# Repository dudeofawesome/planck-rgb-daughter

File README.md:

# planck-rgb-daughter

Daughter-board to add RGB switch lighting to the [OLKB Planck Keyboard](https://olkb.com/planck)

## Libraries used
- adafruit
- capacitor-wima
- resistor
- SparkFun Aesthetics
- SparkFun-Connectors
- SparkFun-PowerSymbols

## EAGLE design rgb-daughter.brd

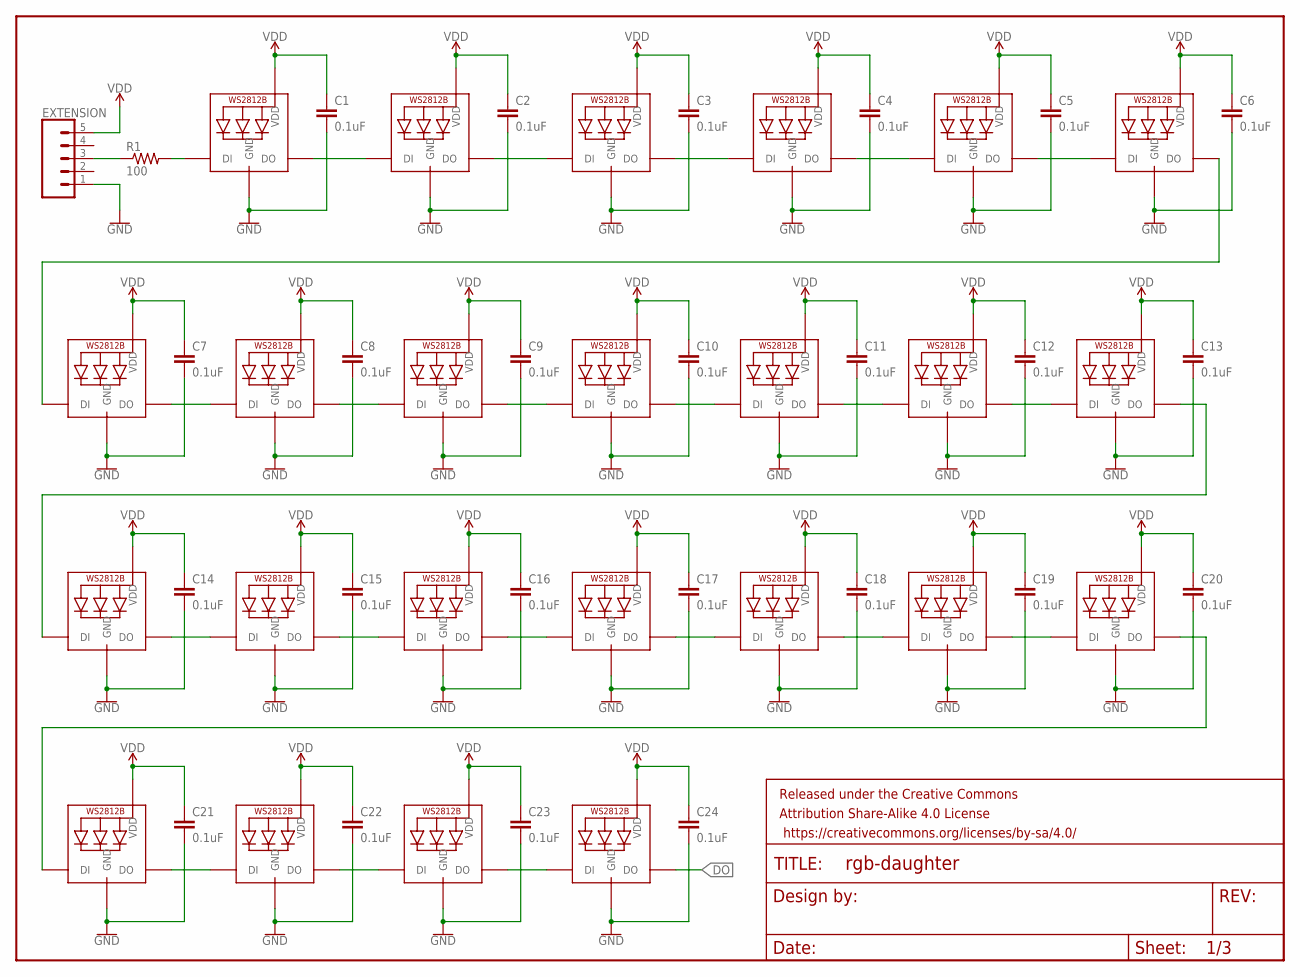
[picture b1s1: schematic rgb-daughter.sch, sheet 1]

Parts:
C1, C2, C3, C4, C5, C6, C7, C8, C9, C10, C11, C12, C13, C14, C15, C16, C17, C18, C19, C20, C21, C22, C23, C24: 0.1uF; 0603
EXTENSION: CONN_051.27MM; 1X05_1.27MM
FRAME1: FRAME-LETTER; CREATIVE_COMMONS
LED1, LED2, LED3, LED4, LED5, LED6, LED7, LED8, LED9, LED10, LED11, LED12, LED13, LED14, LED15, LED16, LED17, LED18, LED19, LED20, LED21, LED22, LED23, LED24: WS2812B3535; LED3535
R1: 100; M0805

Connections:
DO: LED24.3 (DO); also elsewhere on the board
GND: C1.2, C2.2, C3.2, C4.2, C5.2, C6.2, C7.2, C8.2, C9.2, C10.2, C11.2, C12.2, C13.2, C14.2, C15.2, C16.2, C17.2, C18.2, C19.2, C20.2, C21.2, C22.2, C23.2, C24.2, EXTENSION.1, LED1.4 (GND), LED2.4 (GND), LED3.4 (GND), LED4.4 (GND), LED5.4 (GND), LED6.4 (GND), LED7.4 (GND), LED8.4 (GND), LED9.4 (GND), LED10.4 (GND), LED11.4 (GND), LED12.4 (GND), LED13.4 (GND), LED14.4 (GND), LED15.4 (GND), LED16.4 (GND), LED17.4 (GND), LED18.4 (GND), LED19.4 (GND), LED20.4 (GND), LED21.4 (GND), LED22.4 (GND), LED23.4 (GND), LED24.4 (GND); also elsewhere on the board
unnamed: LED1.1 (DI), R1.2
unnamed: LED1.3 (DO), LED2.1 (DI)
unnamed: EXTENSION.3, R1.1
unnamed: LED2.3 (DO), LED3.1 (DI)
unnamed: LED3.3 (DO), LED4.1 (DI)
unnamed: LED4.3 (DO), LED5.1 (DI)
unnamed: LED5.3 (DO), LED6.1 (DI)
unnamed: LED7.3 (DO), LED8.1 (DI)
unnamed: LED8.3 (DO), LED9.1 (DI)
unnamed: LED9.3 (DO), LED10.1 (DI)
unnamed: LED10.3 (DO), LED11.1 (DI)
unnamed: LED11.3 (DO), LED12.1 (DI)
unnamed: LED12.3 (DO), LED13.1 (DI)
unnamed: LED13.3 (DO), LED14.1 (DI)
unnamed: LED14.3 (DO), LED15.1 (DI)
unnamed: LED15.3 (DO), LED16.1 (DI)
unnamed: LED16.3 (DO), LED17.1 (DI)
unnamed: LED17.3 (DO), LED18.1 (DI)
unnamed: LED18.3 (DO), LED19.1 (DI)
unnamed: LED19.3 (DO), LED20.1 (DI)
unnamed: LED20.3 (DO), LED21.1 (DI)
unnamed: LED21.3 (DO), LED22.1 (DI)
unnamed: LED22.3 (DO), LED23.1 (DI)
unnamed: LED23.3 (DO), LED24.1 (DI)
unnamed: LED6.3 (DO), LED7.1 (DI)
VDD: C1.1, C2.1, C3.1, C4.1, C5.1, C6.1, C7.1, C8.1, C9.1, C10.1, C11.1, C12.1, C13.1, C14.1, C15.1, C16.1, C17.1, C18.1, C19.1, C20.1, C21.1, C22.1, C23.1, C24.1, EXTENSION.5, LED1.2 (VDD), LED2.2 (VDD), LED3.2 (VDD), LED4.2 (VDD), LED5.2 (VDD), LED6.2 (VDD), LED7.2 (VDD), LED8.2 (VDD), LED9.2 (VDD), LED10.2 (VDD), LED11.2 (VDD), LED12.2 (VDD), LED13.2 (VDD), LED14.2 (VDD), LED15.2 (VDD), LED16.2 (VDD), LED17.2 (VDD), LED18.2 (VDD), LED19.2 (VDD), LED20.2 (VDD), LED21.2 (VDD), LED22.2 (VDD), LED23.2 (VDD), LED24.2 (VDD); also elsewhere on the board

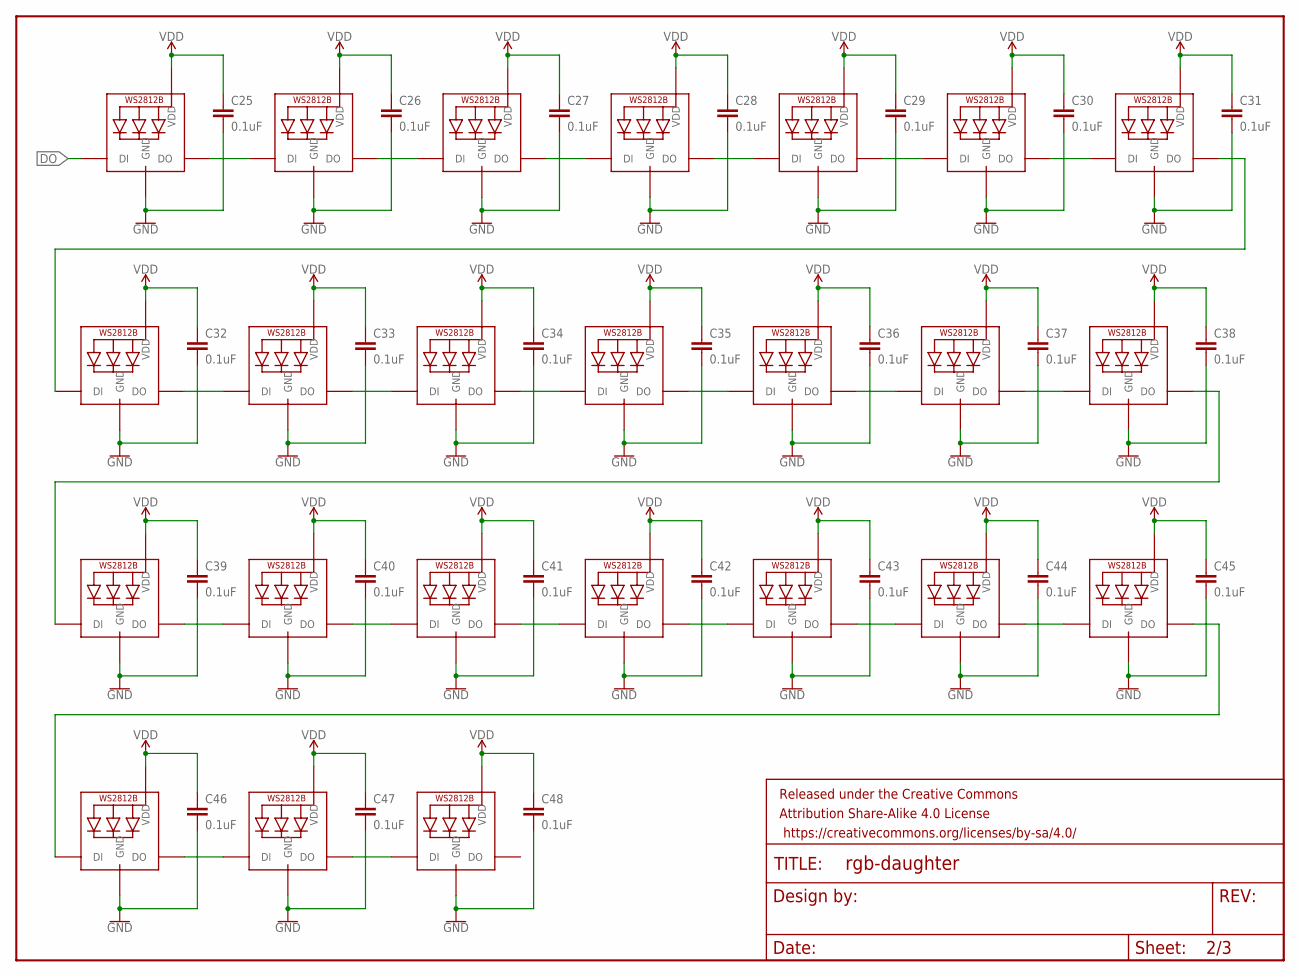
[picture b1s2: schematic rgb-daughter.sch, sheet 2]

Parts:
C25, C26, C27, C28, C29, C30, C31, C32, C33, C34, C35, C36, C37, C38, C39, C40, C41, C42, C43, C44, C45, C46, C47, C48: 0.1uF; 0603
FRAME2: FRAME-LETTER; CREATIVE_COMMONS
LED25, LED26, LED27, LED28, LED29, LED30, LED31, LED32, LED33, LED34, LED35, LED36, LED37, LED38, LED39, LED40, LED41, LED42, LED43, LED44, LED45, LED46, LED47, LED48: WS2812B3535; LED3535

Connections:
DO: LED25.1 (DI); also elsewhere on the board
GND: C25.2, C26.2, C27.2, C28.2, C29.2, C30.2, C31.2, C32.2, C33.2, C34.2, C35.2, C36.2, C37.2, C38.2, C39.2, C40.2, C41.2, C42.2, C43.2, C44.2, C45.2, C46.2, C47.2, C48.2, LED25.4 (GND), LED26.4 (GND), LED27.4 (GND), LED28.4 (GND), LED29.4 (GND), LED30.4 (GND), LED31.4 (GND), LED32.4 (GND), LED33.4 (GND), LED34.4 (GND), LED35.4 (GND), LED36.4 (GND), LED37.4 (GND), LED38.4 (GND), LED39.4 (GND), LED40.4 (GND), LED41.4 (GND), LED42.4 (GND), LED43.4 (GND), LED44.4 (GND), LED45.4 (GND), LED46.4 (GND), LED47.4 (GND), LED48.4 (GND); also elsewhere on the board
unnamed: LED25.3 (DO), LED26.1 (DI)
unnamed: LED26.3 (DO), LED27.1 (DI)
unnamed: LED27.3 (DO), LED28.1 (DI)
unnamed: LED28.3 (DO), LED29.1 (DI)
unnamed: LED29.3 (DO), LED30.1 (DI)
unnamed: LED30.3 (DO), LED31.1 (DI)
unnamed: LED31.3 (DO), LED32.1 (DI)
unnamed: LED32.3 (DO), LED33.1 (DI)
unnamed: LED33.3 (DO), LED34.1 (DI)
unnamed: LED34.3 (DO), LED35.1 (DI)
unnamed: LED35.3 (DO), LED36.1 (DI)
unnamed: LED36.3 (DO), LED37.1 (DI)
unnamed: LED37.3 (DO), LED38.1 (DI)
unnamed: LED38.3 (DO), LED39.1 (DI)
unnamed: LED39.3 (DO), LED40.1 (DI)
unnamed: LED40.3 (DO), LED41.1 (DI)
unnamed: LED41.3 (DO), LED42.1 (DI)
unnamed: LED42.3 (DO), LED43.1 (DI)
unnamed: LED43.3 (DO), LED44.1 (DI)
unnamed: LED44.3 (DO), LED45.1 (DI)
unnamed: LED45.3 (DO), LED46.1 (DI)
unnamed: LED46.3 (DO), LED47.1 (DI)
unnamed: LED47.3 (DO), LED48.1 (DI)
VDD: C25.1, C26.1, C27.1, C28.1, C29.1, C30.1, C31.1, C32.1, C33.1, C34.1, C35.1, C36.1, C37.1, C38.1, C39.1, C40.1, C41.1, C42.1, C43.1, C44.1, C45.1, C46.1, C47.1, C48.1, LED25.2 (VDD), LED26.2 (VDD), LED27.2 (VDD), LED28.2 (VDD), LED29.2 (VDD), LED30.2 (VDD), LED31.2 (VDD), LED32.2 (VDD), LED33.2 (VDD), LED34.2 (VDD), LED35.2 (VDD), LED36.2 (VDD), LED37.2 (VDD), LED38.2 (VDD), LED39.2 (VDD), LED40.2 (VDD), LED41.2 (VDD), LED42.2 (VDD), LED43.2 (VDD), LED44.2 (VDD), LED45.2 (VDD), LED46.2 (VDD), LED47.2 (VDD), LED48.2 (VDD); also elsewhere on the board

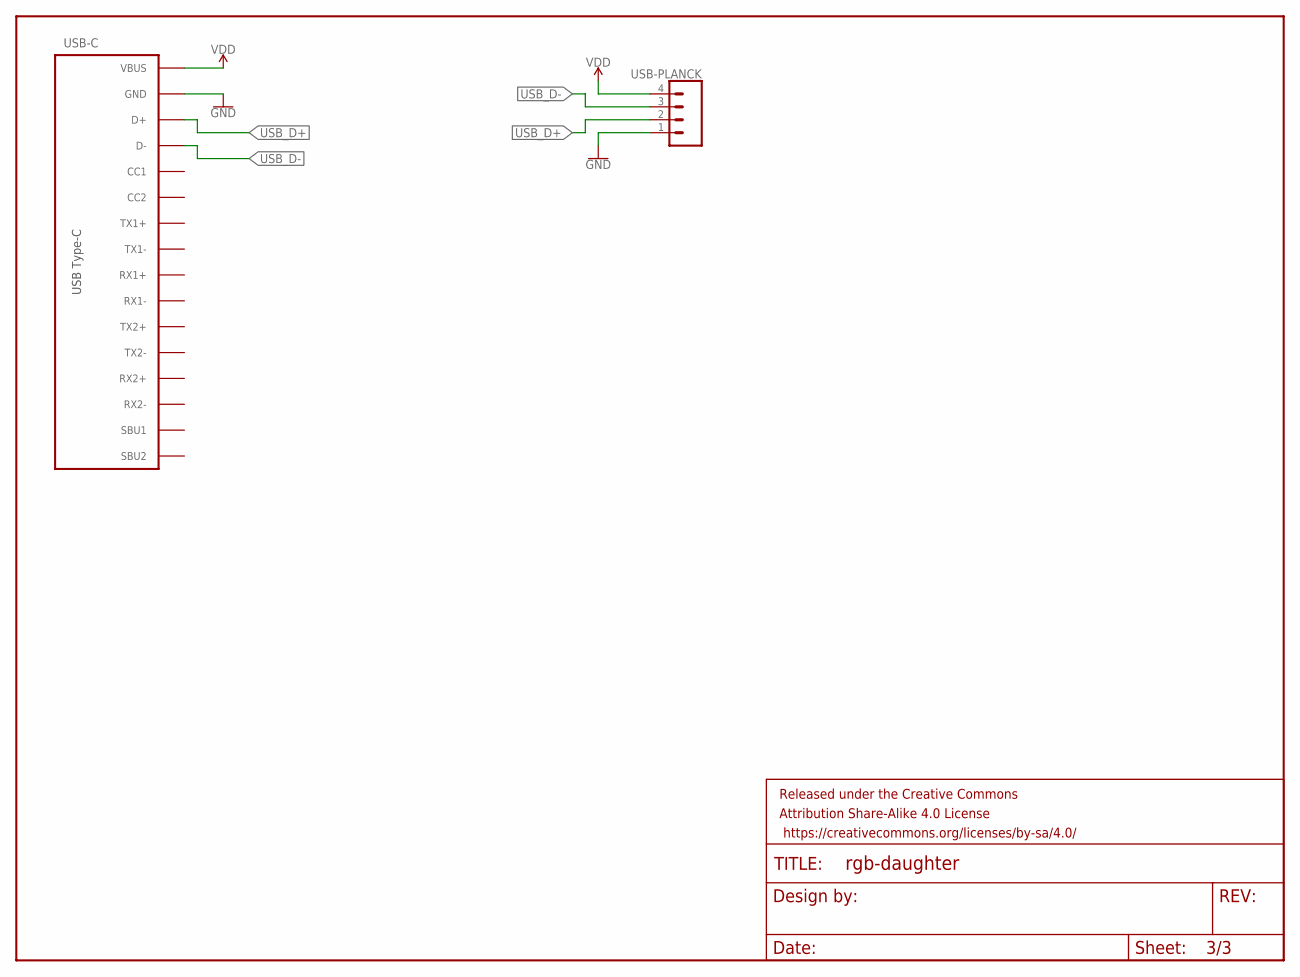
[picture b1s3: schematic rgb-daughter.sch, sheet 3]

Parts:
FRAME3: FRAME-LETTER; CREATIVE_COMMONS
USB-C: USB-TYPE-CDX07S024JJ3R1300; DX07S024JJ3R1300
USB-PLANCK: CONN_041.27MM; 1X04_1.27MM

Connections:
GND: USB-C.A1 (GND), USB-C.A12 (GND), USB-C.B1 (GND), USB-C.B12 (GND), USB-C.GND@1 (GND), USB-C.GND@2 (GND), USB-C.GND@3 (GND), USB-C.GND@4 (GND), USB-C.GND@5 (GND), USB-C.GND@6 (GND), USB-PLANCK.1; also elsewhere on the board
RX1+: USB-C.B11 (RX1+)
SBU2: USB-C.B8 (SBU2)
TX2-: USB-C.B3 (TX2-)
USB_D+: USB-C.A6 (D+), USB-C.B6 (D+), USB-PLANCK.2
USB_D-: USB-C.A7 (D-), USB-C.B7 (D-), USB-PLANCK.3
VDD: USB-C.A4 (VBUS), USB-C.A9 (VBUS), USB-C.B4 (VBUS), USB-C.B9 (VBUS), USB-PLANCK.4; also elsewhere on the board

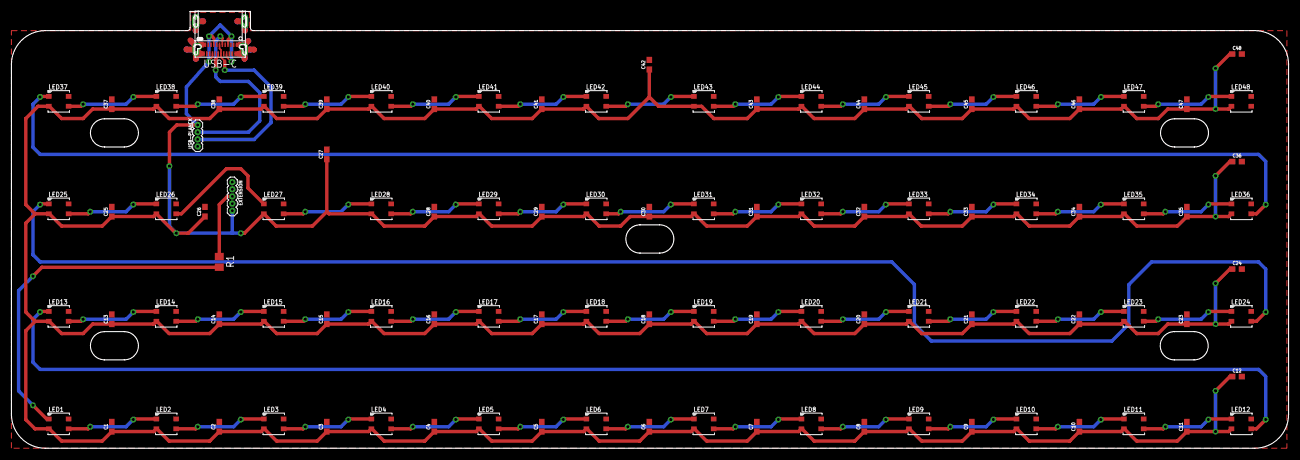
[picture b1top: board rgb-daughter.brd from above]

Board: 2 copper layers, 226.3 x 77.4 mm, 103 parts (1 on the bottom side), 53 nets.

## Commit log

2017-09-29 🎉 Initial commit
2017-09-29 🔧 gitignoring Eagle backups
2017-09-29 📝 listing required libraries
2017-09-29 📝 add short description
2017-10-05 feat(planck): add caps
2017-10-08 ✨ add ws2812b design block
2017-10-09 🐛 rebuilding schematic with design blocks
2017-10-09 🐛 moving ws2812b's under LED holes
2017-10-09 🔧 updating gitignore
2017-10-09 ✨ initial routing work
2017-10-09 ✨ finished routing
2017-10-09 🐛 moving caps to avoid contact with switches
2017-10-09 🔥 removing test cherry switch
2017-10-10 🐛 resizing and moving traces
2017-10-10 🔥 removing guide markings
2017-10-11 ⏪ Revert "🔥 removing guide markings"
    This reverts commit a025655127d8e2d90611e41790c7fbea721f61e7.
2017-10-11 ⏪ Revert "🔥 removing test cherry switch"
    This reverts commit f0bcf8e92973c98fa4b33c8b3d8bb0c59f9eaaca.
2017-10-11 🚧📦 using ws2812b 3535
    routes are currently screwed up
2017-10-11 🐛 moving LEDs
2017-10-11 🐛 adding cutouts for standoffs
2017-10-11 🚧✨ adds routes
2017-10-11 🚧✨ add VCC routes
2017-10-11 🚧✨ add GND routes
2017-10-11 ✨ connect rows with VCC and GND
2017-10-11 🚨 resize drill holes
2017-10-11 💄 add header pin labels
2017-10-11 🐛 fix center standoff cutout position
2017-10-11 ✨ connect rows' data
2017-10-11 ✨ add data routes between LEDs
2017-10-11 💄 converting text labels to attributes
2017-10-11 💄 adding logo
2017-10-11 📝 adding description
2017-10-12 🔧🔥 ignore eagle.epf
2017-10-17 🚧✨ create USB Type-C part
2017-10-18 🔧 change USB units to mm
2017-10-18 🐛 fix pad placement
2017-10-18 🚧✨ add mounting holes
2017-10-18 🔥 remove old packages
2017-10-18 ✨ add mounting holes
2017-10-18 💄 resize package outline
2017-10-18 💄 add markings on package
2017-10-18 💄 fix package outline
2017-10-18 ⬆️ updating USB Type-C package
2017-10-19 🐛 fix USB-C drills
    - add proper drills for USB-C package
    - route drills to GND
2017-10-19 💄 add name to package and symbol
2017-10-19 👽 update for new USB-C package
    - connect new pins on USB-C
    - move USB-C package to match placement in case
2017-10-19 🚧✨ routing USB-C connector
2017-10-19 🐛 fixing DRC error
2017-10-19 ✨ connecting GND pour to USB-C
2017-10-19 🚧🐛 fixing routing issues with connector
2017-10-19 💄 using GND pour on top layer
2017-10-19 🐛 fix LED numbering
2017-10-19 💄 moving logo
2017-10-19 💄🐛 moving wire to avoid issue with logo
2017-10-19 🐛 moving components to avoid Planck components
2017-10-19 🐛 fix USB-C pad layout
    - D+ and D- were swapped
    - simplify USB-C symbol
2017-10-19 ✨ add cheap version of USB-C SMT package
2017-10-24 📦 add Planck milled bottom

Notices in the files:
parts and their libraries:
SparkFun-Aesthetics: Licensing: Creative Commons ShareAlike 4.0 International - https://creativecommons.org/licenses/by-sa/4.0
SparkFun-Aesthetics: Released under the Creative Commons Attribution Share-Alike 4.0 License
SparkFun-Aesthetics: https://creativecommons.org/licenses/by-sa/4.0
